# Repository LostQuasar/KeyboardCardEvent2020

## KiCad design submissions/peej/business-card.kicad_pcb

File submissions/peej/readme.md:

# Peej's Business card

One of the more interesting developments in custom keyboard kits in the last few years has been the abundance of through hole component kits. Starting with the Planck THK and then the Plaid, there are now many kits in various layouts to suit all corners of the hobby.

The great thing about these kits is that anyone with basic soldering skills and equipment can build an entire board from a bare PCB and bag of components.

This PCB business card continues this trend with a 4 key Plaid style macropad.

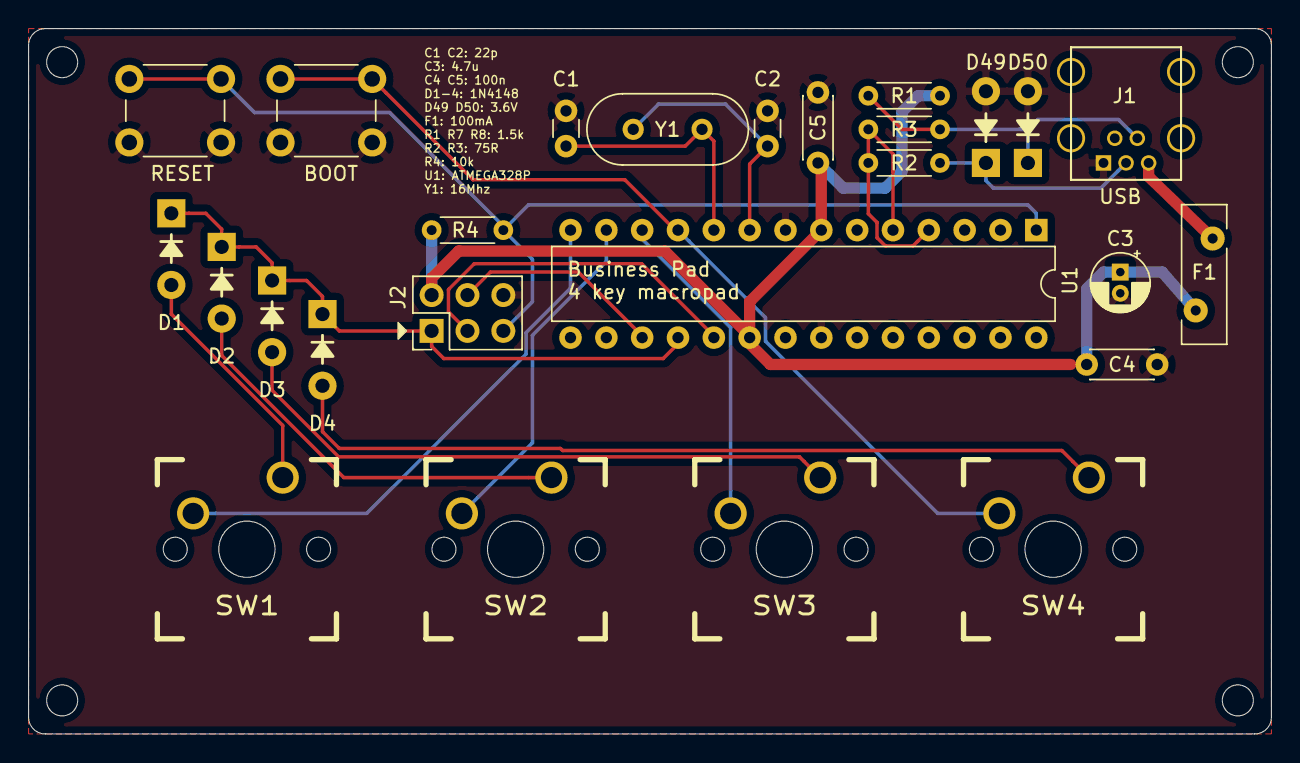
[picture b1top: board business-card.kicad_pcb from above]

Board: 2 copper layers, 88.1 x 50.0 mm, 30 parts (0 on the bottom side), 21 nets.

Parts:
C1, C2: 20p; C_Disc_D3.0mm_W1.6mm_P2.50mm
C3: 4.7u; CP_Radial_D4.0mm_P1.50mm
C4, C5: 100n; C_Disc_D4.3mm_W1.9mm_P5.00mm
D1, D2, D3, D4: 1N4148; DIODE
D49, D50: 3.6V; DIODE
F1: 100mA; Fuse_Bourns_MF-RHT100
H1, H2, H3, H4: M2; MountingHole_2.2mm_M2
J1: USB_OTG; USB_Mini-B
J2: AVR_ISP_6; PinHeader_2x03_P2.54mm_Vertical
R1: 1.5k; R_Axial_DIN0204_L3.6mm_D1.6mm_P5.08mm_Horizontal
R2, R3: 75R; R_Axial_DIN0204_L3.6mm_D1.6mm_P5.08mm_Horizontal
R4: 10k; R_Axial_DIN0204_L3.6mm_D1.6mm_P5.08mm_Horizontal
SW1, SW2, SW3, SW4: SW_Push; MX
SW50: RESET; SW_PUSH_6mm
SW51: BOOT; SW_PUSH_6mm
U1: ATMEGA328-PU; DIP-28_W7.62mm
Y1: 16MHz; Crystal_HC49-4H_Vertical

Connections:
+5V: C3.1, C4.1, C5.1, F1.2, J2.2, R1.2, R4.1, U1.7, U1.20
/COL0: SW1.2, U1.14
/COL1: SW2.2, U1.13
/COL2: SW3.2, U1.12
/COL3: SW4.2, SW51.1, U1.11
/RESET: J2.5, R4.2, SW50.1, U1.1
/ROW0: D1.1, D2.1, D3.1, D4.1, J2.1, U1.18
/USB_D+: R2.1, U1.4
/USB_D-: R3.1, U1.5
GND: C1.2, C2.2, C3.2, C4.2, C5.2, D49.2, D50.2, J1.5, J2.6, SW50.2, SW51.2, U1.8, U1.22
unnamed: C1.1, U1.10, Y1.2
unnamed: C2.1, U1.9, Y1.1
unnamed: D1.2, SW1.1
unnamed: D2.2, SW2.1
unnamed: D3.2, SW3.1
unnamed: D4.2, SW4.1
unnamed: D49.1, J1.3, R2.2
unnamed: D50.1, J1.2, R1.1, R3.2
unnamed: F1.1, J1.1
unnamed: J2.3, U1.19
unnamed: J2.4, U1.17

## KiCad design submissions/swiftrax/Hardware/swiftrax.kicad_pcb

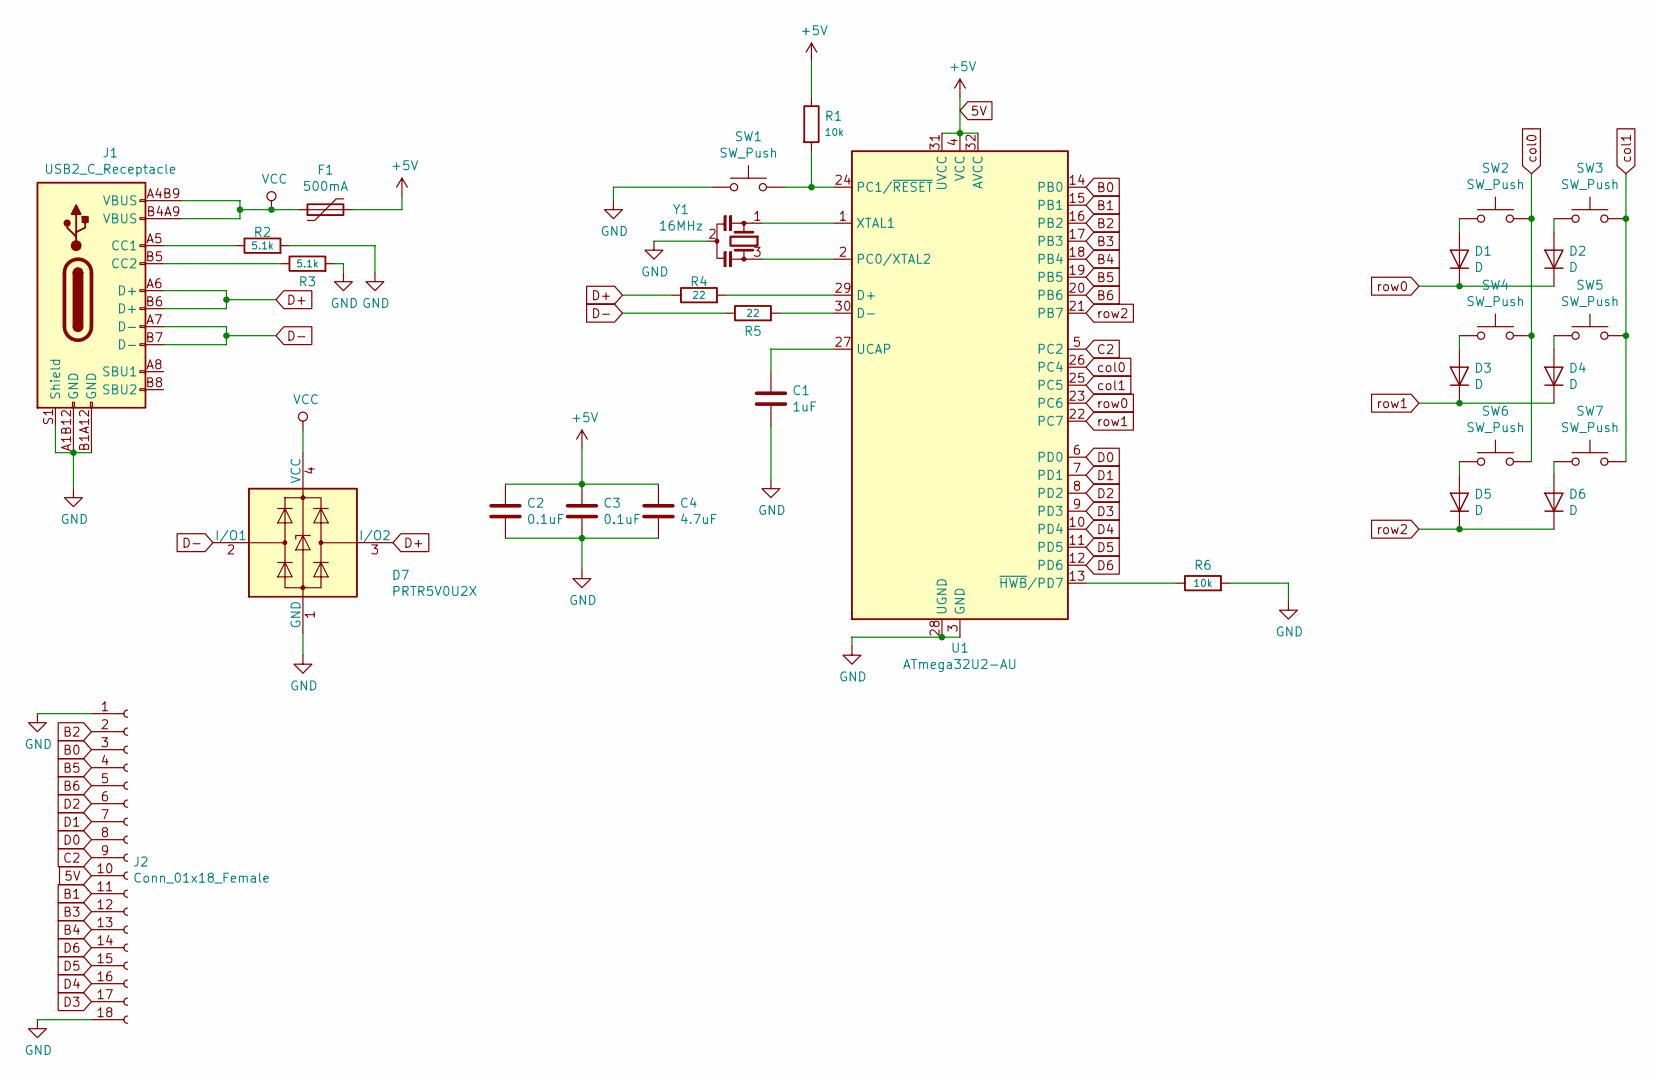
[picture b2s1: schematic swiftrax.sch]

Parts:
C1: 1uF; C_0805_2012Metric
C2, C3: 0.1uF; C_0805_2012Metric
C4: 4.7uF; C_0805_2012Metric
D1, D2, D3, D4, D5, D6: D; D_SOD-123
D7: PRTR5V0U2X; SOT-143
F1: 500mA; Fuse_1206_3216Metric
J1: USB2_C_Receptacle; Mid_Mount-USB_C_HandSoldering
J2: Conn_01x18_Female; BreakOutPins
R1, R6: 10k; R_0805_2012Metric
R2, R3: 5.1k; R_0805_2012Metric
R4, R5: 22; R_0805_2012Metric
SW1: SW_Push; SKQG-1155865
SW2, SW3, SW4, SW5, SW6, SW7: SW_Push; SW_Cherry_MX_1.00u_PCB
U1: ATmega32U2-AU; TQFP-32_7x7mm_P0.8mm
Y1: 16MHz; Resonator_SMD_muRata_CSTxExxV-3Pin_3.0x1.1mm_HandSoldering_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

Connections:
5V: C2.1, C3.1, C4.1, F1.2, J2.10, R1.1, U1.4 (VCC), U1.31 (UVCC), U1.32 (AVCC)
B0: J2.3, U1.14 (PB0)
B1: J2.11, U1.15 (PB1)
B2: J2.2, U1.16 (PB2)
B3: J2.12, U1.17 (PB3)
B4: J2.13, U1.18 (PB4)
B5: J2.4, U1.19 (PB5)
B6: J2.5, U1.20 (PB6)
C2: J2.9, U1.5 (PC2)
D0: J2.8, U1.6 (PD0)
D1: J2.7, U1.7 (PD1)
D2: J2.6, U1.8 (PD2)
D3: J2.17, U1.9 (PD3)
D4: J2.16, U1.10 (PD4)
D5: J2.15, U1.11 (PD5)
D6: J2.14, U1.12 (PD6)
D+: D7.3 (I/O2), J1.A6 (D+), J1.B6 (D+), R4.1
D-: D7.2 (I/O1), J1.A7 (D-), J1.B7 (D-), R5.1
GND: C1.2, C2.2, C3.2, C4.2, D7.1 (GND), J1.A1B12 (GND), J1.B1A12 (GND), J1.S1 (Shield), J2.1, J2.18, R2.2, R3.2, R6.2, SW1.1, U1.3 (GND), U1.28 (UGND), Y1.2
unnamed: C1.1, U1.27 (UCAP)
unnamed: D1.2 (A), SW2.1
unnamed: D2.2 (A), SW3.1
unnamed: D3.2 (A), SW4.1
unnamed: D4.2 (A), SW5.1
unnamed: D5.2 (A), SW6.1
unnamed: D6.2 (A), SW7.1
unnamed: J1.A5 (CC1), R2.1
unnamed: J1.B5 (CC2), R3.1
unnamed: R1.2, SW1.2, U1.24 (PC1/~RESET)
unnamed: R4.2, U1.29 (D+)
unnamed: R5.2, U1.30 (D-)
unnamed: R6.1, U1.13 (~HWB~/PD7)
unnamed: U1.1 (XTAL1), Y1.1
unnamed: U1.2 (PC0/XTAL2), Y1.3
VCC: D7.4 (VCC), F1.1, J1.A4B9 (VBUS), J1.B4A9 (VBUS)
col0: SW2.2, SW4.2, SW6.2, U1.26 (PC4)
col1: SW3.2, SW5.2, SW7.2, U1.25 (PC5)
row0: D1.1 (K), D2.1 (K), U1.23 (PC6)
row1: D3.1 (K), D4.1 (K), U1.22 (PC7)
row2: D5.1 (K), D6.1 (K), U1.21 (PB7)

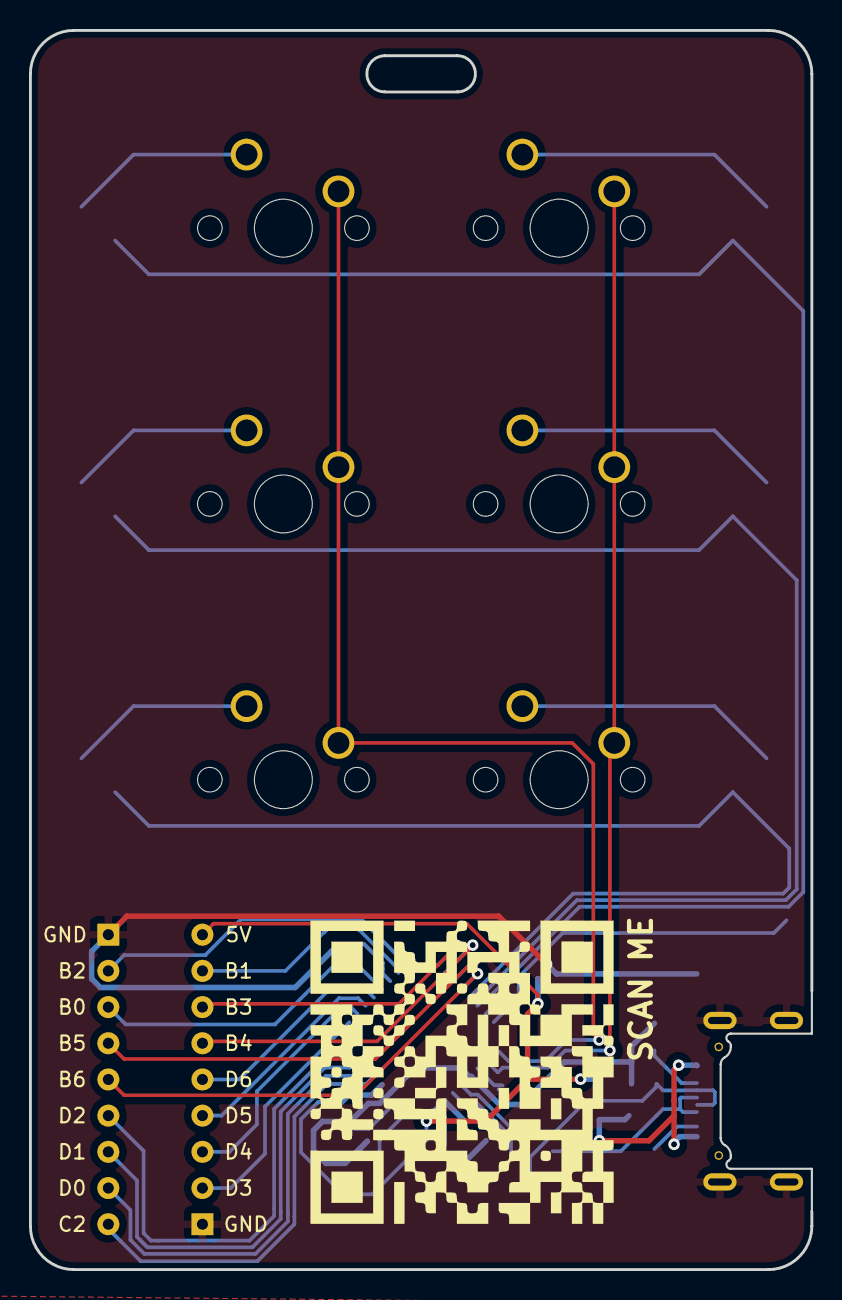
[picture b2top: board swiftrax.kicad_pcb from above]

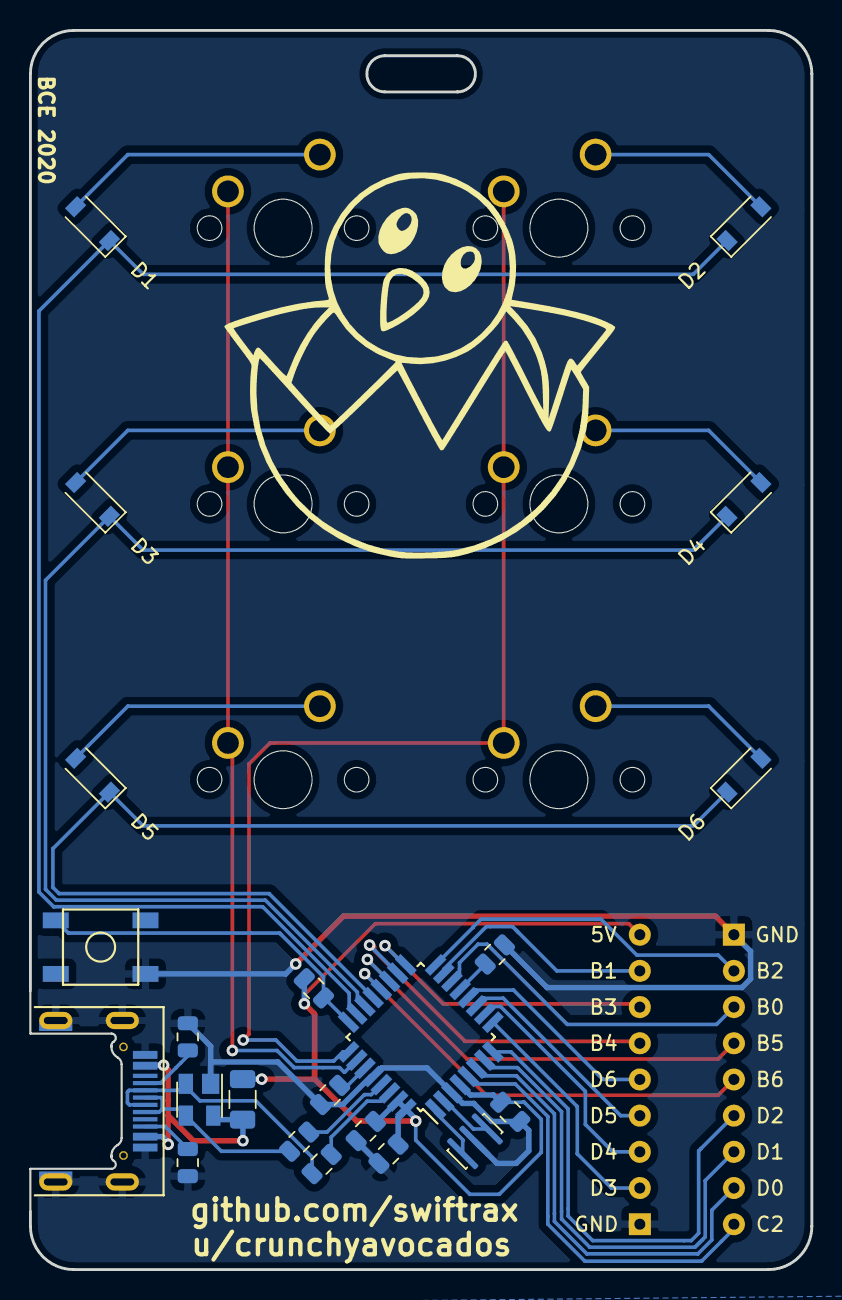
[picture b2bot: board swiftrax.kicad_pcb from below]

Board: 2 copper layers, 54.0 x 85.6 mm, 29 parts (28 on the bottom side), 40 nets.
